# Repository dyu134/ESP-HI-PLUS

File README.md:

# ESP-HI-PLUS

An **AI-enabled voice assistant with on-screen interaction**, built around the **ESP32-S3-WROOM-1**. The board integrates a microphone, speaker amplifier, IMU, 2" IPS LCD, MicroSD card slot, and USB-C with on-board Li-ion battery charging, and exposes **two 5-pin magnetic pogo-pin connectors** for attaching various sub-modules. Designed for handheld and wearable applications that combine on-device conversational AI, audio capture/playback, display feedback, and motion sensing.

## Features

### Core Compute

- **ESP32-S3-WROOM-1** (U2) — 32-bit dual-core LX7 MCU with Wi-Fi 4, BLE 5 (LE), and a rich peripheral set including I2S, I2C, SPI, and USB.

### Sensors

- **LSM6DSV16X** 6-axis IMU (U8) — 3-axis accelerometer + 3-axis gyroscope with I3C/I2C/SPI interface for motion tracking.
- **ICS-43434 I2S Microphone** (MK1) — digital MEMS microphone over I2S for audio capture.

### Audio Output

- **MAX98357A** Class-D I2S amplifier (U7) — drives an external speaker (LS1) with no required MCLK.
- **PicoBlade speaker connector** (LS1) for an off-board speaker.

### Power

- **USB-C input** (J1) with **USBLC6-2P6** ESD protection (D1/D7/D8).
- **TP4065** linear Li-ion/Li-Po charger (U5) — single-cell charging from USB.
- **TLV75733PDBV** 3.3 V LDO (U3) — system rail for the MCU and logic.
- **MAX40200AUK** ideal-diode OR-ing (U1, U6) — seamless USB / battery switching with low dropout.
- **PicoBlade battery connector** (BT1) for a single-cell Li-ion / Li-Po pack.
- **PMEG4010CEJ** Schottky diode (D5) and **MF-MSMF200** PTC fuse (F1) for input/battery protection.
- **SMF6.8CA** TVS diode (D6) for transient suppression.

### User Interface

- **[2" LCD header](https://www.waveshare.com/2inch-LCD-Module.htm)** (J2) — 2" IPS LCD display.
- **MicroSD Card Slot** (J5) — for local storage of audio, logs, or assets.
- **Two SKRPACE010 tactile pushbuttons** (SW1, SW2).
- **JS102011SAQN SPDT slide switch** (SW3).
- **WS2812B-2020** addressable RGB LED (D12), plus discrete status LEDs (D2 orange for battery charging, D4 red for USB power).
- **Two PR5L4015-5P-C-F magnetic pogo-pin connectors** (J3, J4) — 5-pin 2.54 mm headers that mate with **magnetic pogo-pin sub-modules** for snap-on expansion.

### Mounting

- Four M2 slim mounting holes (H1–H4).

## Sub-Module Identification

The ESP-HI-PLUS uses a two-stage detection system (analog ID resistor + I²C EEPROM metadata) to identify and configure attached sub-modules.

Detailed technical specifications for the identification protocol, class table, and EEPROM metadata can be found in the [Sub-modules directory](./Sub-modules/README.md).

## Available Sub-modules

- **[Desktop](./Sub-modules/Desktop/README.md)** — A desktop alarm clock and environment monitor featuring temperature, humidity, and presence sensing.

See the [Sub-modules directory](./Sub-modules/README.md) for technical specifications and the full list of supported classes.

## Repository Layout

```text
.
├── ESP-HI-PLUS.kicad_pro       # KiCad project file
├── ESP-HI-PLUS.kicad_sch       # Schematic
├── ESP-HI-PLUS.kicad_pcb       # PCB layout
├── Sub-modules/                # Snap-on expansion boards
│   └── Desktop/                # Desktop alarm clock / environment monitor
├── fp-lib-table                # Footprint library table
├── sym-lib-table               # Symbol library table
├── fabrication-toolkit-options.json
├── ESP-HI-PLUS Symbols/        # Project-local schematic symbols
├── ESP-HI-PLUS Footprints/     # Project-local footprint libraries (*.pretty)
├── ESP-HI-PLUS 3D Models/      # STEP models used by the 3D viewer
├── production/                 # Manufacturing outputs
    ├── bom.csv                 # Bill of materials
    ├── designators.csv         # Reference designators
    ├── positions.csv           # Pick-and-place positions
    ├── netlist.ipc             # IPC-D-356 netlist
    └── ESP-HI-PLUS_v1.17.zip   # Production archive (latest)
```

## Bill of Materials (summary)

| Refs        | Description                                                                                  |
|-------------|----------------------------------------------------------------------------------------------|
| U2          | ESP32-S3-WROOM-1 module                                                                      |
| U3          | TLV75733PDBV — 3.3 V LDO                                                                     |
| U5          | TP4065 — Li-ion charger                                                                      |
| MK1         | ICS-43434 I2S microphone                                                                     |
| U7          | MAX98357A — I2S Class-D amplifier                                                            |
| U8          | LSM6DSV16X — 6-axis IMU                                                                      |
| U1, U6      | MAX40200AUK — ideal diode                                                                    |
| D1/D7/D8    | USBLC6-2P6 — USB ESD TVS array                                                               |
| D12         | WS2812B-2020 — addressable RGB LED                                                           |
| J1          | USB-C receptacle                                                                             |
| J2          | [2" IPS LCD connector](https://www.waveshare.com/2inch-LCD-Module.htm)                       |
| J3, J4      | Two 5-pin magnetic pogo-pin connectors (PR5L4015-5P-C-F) for sub-modules                     |
| J5          | MicroSD Card Slot (Hirose DM3AT)                                                             |
| SW1, SW2    | SKRPACE010 tactile pushbuttons                                                               |
| SW3         | JS102011SAQN SPDT slide switch                                                               |
| R28, R29    | 47 kΩ sub-module **AUX1/ID0** detection resistors (0402) — divider used for ADC class lookup |

See `production/bom.csv` for the full BOM with footprints and quantities.

## Getting Started

1. Open `ESP-HI-PLUS.kicad_pro` in KiCad 8 or later.
2. Review the schematic (`ESP-HI-PLUS.kicad_sch`) and PCB (`ESP-HI-PLUS.kicad_pcb`).
3. Re-generate fabrication outputs as needed (Gerbers, drill files, pick-and-place).
4. Flash the ESP32-S3 via the USB-C port using ESP-IDF or Arduino.

## Manufacturing Outputs

The `production/` folder contains ready-to-use outputs for the latest **v1.17** revision:

- **`bom.csv`** — bill of materials for sourcing.
- **`positions.csv`** — pick-and-place rotation/coordinates for SMT assembly.
- **`netlist.ipc`** — IPC-D-356 test netlist.
- **`ESP-HI-PLUS_v1.17.zip`** — full fabrication archive (Gerbers + drill included).

## License

License not specified. Add a `LICENSE` file if you intend to distribute this design.

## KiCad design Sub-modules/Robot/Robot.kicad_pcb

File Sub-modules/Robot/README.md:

# Robot Sub-module

The **Robot** sub-module is a high-performance actuator and sensing expansion board for the **ESP-HI-PLUS**, designed to transform the device into a mobile or interactive robotic platform. Powered by an RP2040 MCU, it handles real-time motor control, battery management, and inertial sensing.

*(Space for 3D Model Image)*

## Features

### Core Compute

- **RP2040** (U3) — Dual-core ARM Cortex-M0+ microcontroller for real-time servo PWM generation and sensor processing.
- **16 Mbit Flash** (U?) — Storage for RP2040 firmware.

### Actuation & Sensing

- **Servo Support** (M1–M4) — High-current outputs for up to 4 high-torque servo motors (e.g., MG996R).
- **LSM6DSV16X** (U8) — 6-axis IMU with embedded sensor fusion and Machine Learning Core for orientation and motion detection.
- **INA3221** (U11) — Triple-channel current and voltage monitor for real-time tracking of servo and system power consumption.

### Power Management

- **TLV75733PDBV** (U4) — 3.3V Low-Dropout (LDO) regulator providing stable power to the MCU and peripherals.
- **MAX17049** (U5) — 2-cell Li-ion battery fuel gauge with ModelGauge m5 algorithm for accurate state-of-charge reporting.
- **MAX40200AUK** (U2) — Ultra-low voltage drop ideal diode for efficient power path management.
- **UBEC Input** — Support for external 5V UBEC to power high-current servos from the battery.
- **XT60 Connector** (J4) — High-current battery interface (typically 2S Li-ion).

### User Interface & IO

- **SK9822-EC20** (D6) — Addressable RGB LED for status or mood lighting.
- **SKRPACE010** (SW3, SW?) — Tactile switches for reset, boot mode, or user interaction.

### Identification & Metadata

The Robot module follows the standard [ESP-HI-PLUS identification protocol](../README.md).

- **R_ID (953 kΩ)** — Identifies the module as **Class 1 (Actuator — Servo)**.
- **AT24CS02** (U10) — 2 Kbit I²C EEPROM carrying module metadata and serial number.

#### EEPROM Metadata

| Offset | Size | Field | Value (Hex) | Value (Decoded) | Description |
| :------: | :----: | :------ | :-----------: | :---------------- | :------------ |
| 0x00 | 4 | Magic Number | 45 53 50 4D | "ESPM" | ASCII sanity check |
| 0x04 | 1 | Class ID | 0x01 | 1 | Actuator - Servo |
| 0x05 | 1 | Module ID | 0x03 | 3 | Robot v1 |
| 0x06 | 1 | HW Revision | 0x01 | 1 | First PCB revision |
| 0x07 | 2 | FW Revision | 0x0100 | 1.0 | Major.Minor |
| 0x09 | 1 | Protocol Revision | 0x01 | 1 | Communication protocol v1 |
| 0x0A | 1 | Power Requirement | 0x00 | Self-powered | Powered by 2S battery |
| 0x0B | 2 | Max Current (mA) | 0x07D0 | 2000 mA | Maximum draw (little-endian) |
| 0x0D | 2 | Min Voltage (mV) | 0x1770 | 6000 mV | Minimum supply voltage (2S) |
| 0x0F | 2 | Boot Delay (ms) | 0x0064 | 100 ms | Power-on delay (little-endian) |
| 0x11 | 4 | Capability Bitmask | 0x00000014 | — | Bits 2, 4 enabled (Async, E-Stop) |
| 0x15 | 16 | Module Name | 52 6F 62 6F... | "Robot" | ASCII, null-terminated |
| 0x25 | 16 | Serial Number | 52 42 2D 30... | "RB-001-XXXX" | ASCII, null-terminated |
| 0x35 | 198 | User Data | — | — | Available for custom data |
| 0xFB | 4 | CRC32 | 0xXXXXXXXX | — | CRC32 of bytes 0x00–0xFA |

#### Capability Bitmask (Proposed)

**Value:** `0x00000014`

| Bit | Value | Capability | Status |
| :---: | :---: | :--- | :--- |
| 0 | 0x01 | Needs Calibration | ❌ Disabled |
| 1 | 0x02 | Requires ACK | ❌ Disabled |
| 2 | 0x04 | Async Data | ✅ Enabled |
| 3 | 0x08 | Supports Sleep | ❌ Disabled |
| 4 | 0x10 | Has Emergency Stop | ✅ Enabled |
| 5 | 0x20 | Supports OTA | ❌ Disabled |
| 6 | 0x40 | Has Battery Backup | ❌ Disabled |
| 7 | 0x80 | Requires Bootloader Mode | ❌ Disabled |

## Integration

The Robot module uses an RP2040 to handle low-level PWM and sensor data. It communicates with the ESP-HI-PLUS main board via UART and I²C.

### Pinouts (Magnetic Pogo Connectors)

#### J2 (MAG1)

| Pin | Name   | Description                                           |
| --- | ------ | ----------------------------------------------------- |
| 1   | VMAIN  | 2-way power bus shared with main module               |
| 2   | GND    | Ground                                                |
| 3   | UART RX| Data from main module                                 |
| 4   | UART TX| Data to main module                                   |
| 5   | EN     | Main module control to enable/disable submodule power |

#### J3 (MAG2)

| Pin | Name     | Description                                     |
| --- | -------- | ----------------------------------------------- |
| 1   | I2C SDA  | For reading module ID metadata EEPROM           |
| 2   | I2C SCL  | For reading module ID metadata EEPROM           |
| 3   | AUX1/ID0 | Hardware class identifier resistor              |
| 4   | AUX2     | Auxiliary data pin                              |
| 5   | AUX3     | Auxiliary data pin                              |

## Repository Layout

```text
.
├── Robot.kicad_pro           # KiCad project file
├── Robot.kicad_sch           # Schematic
├── Robot.kicad_pcb           # PCB layout
├── Robot Symbols/            # Project-local schematic symbols
└── README.md                 # This file
```

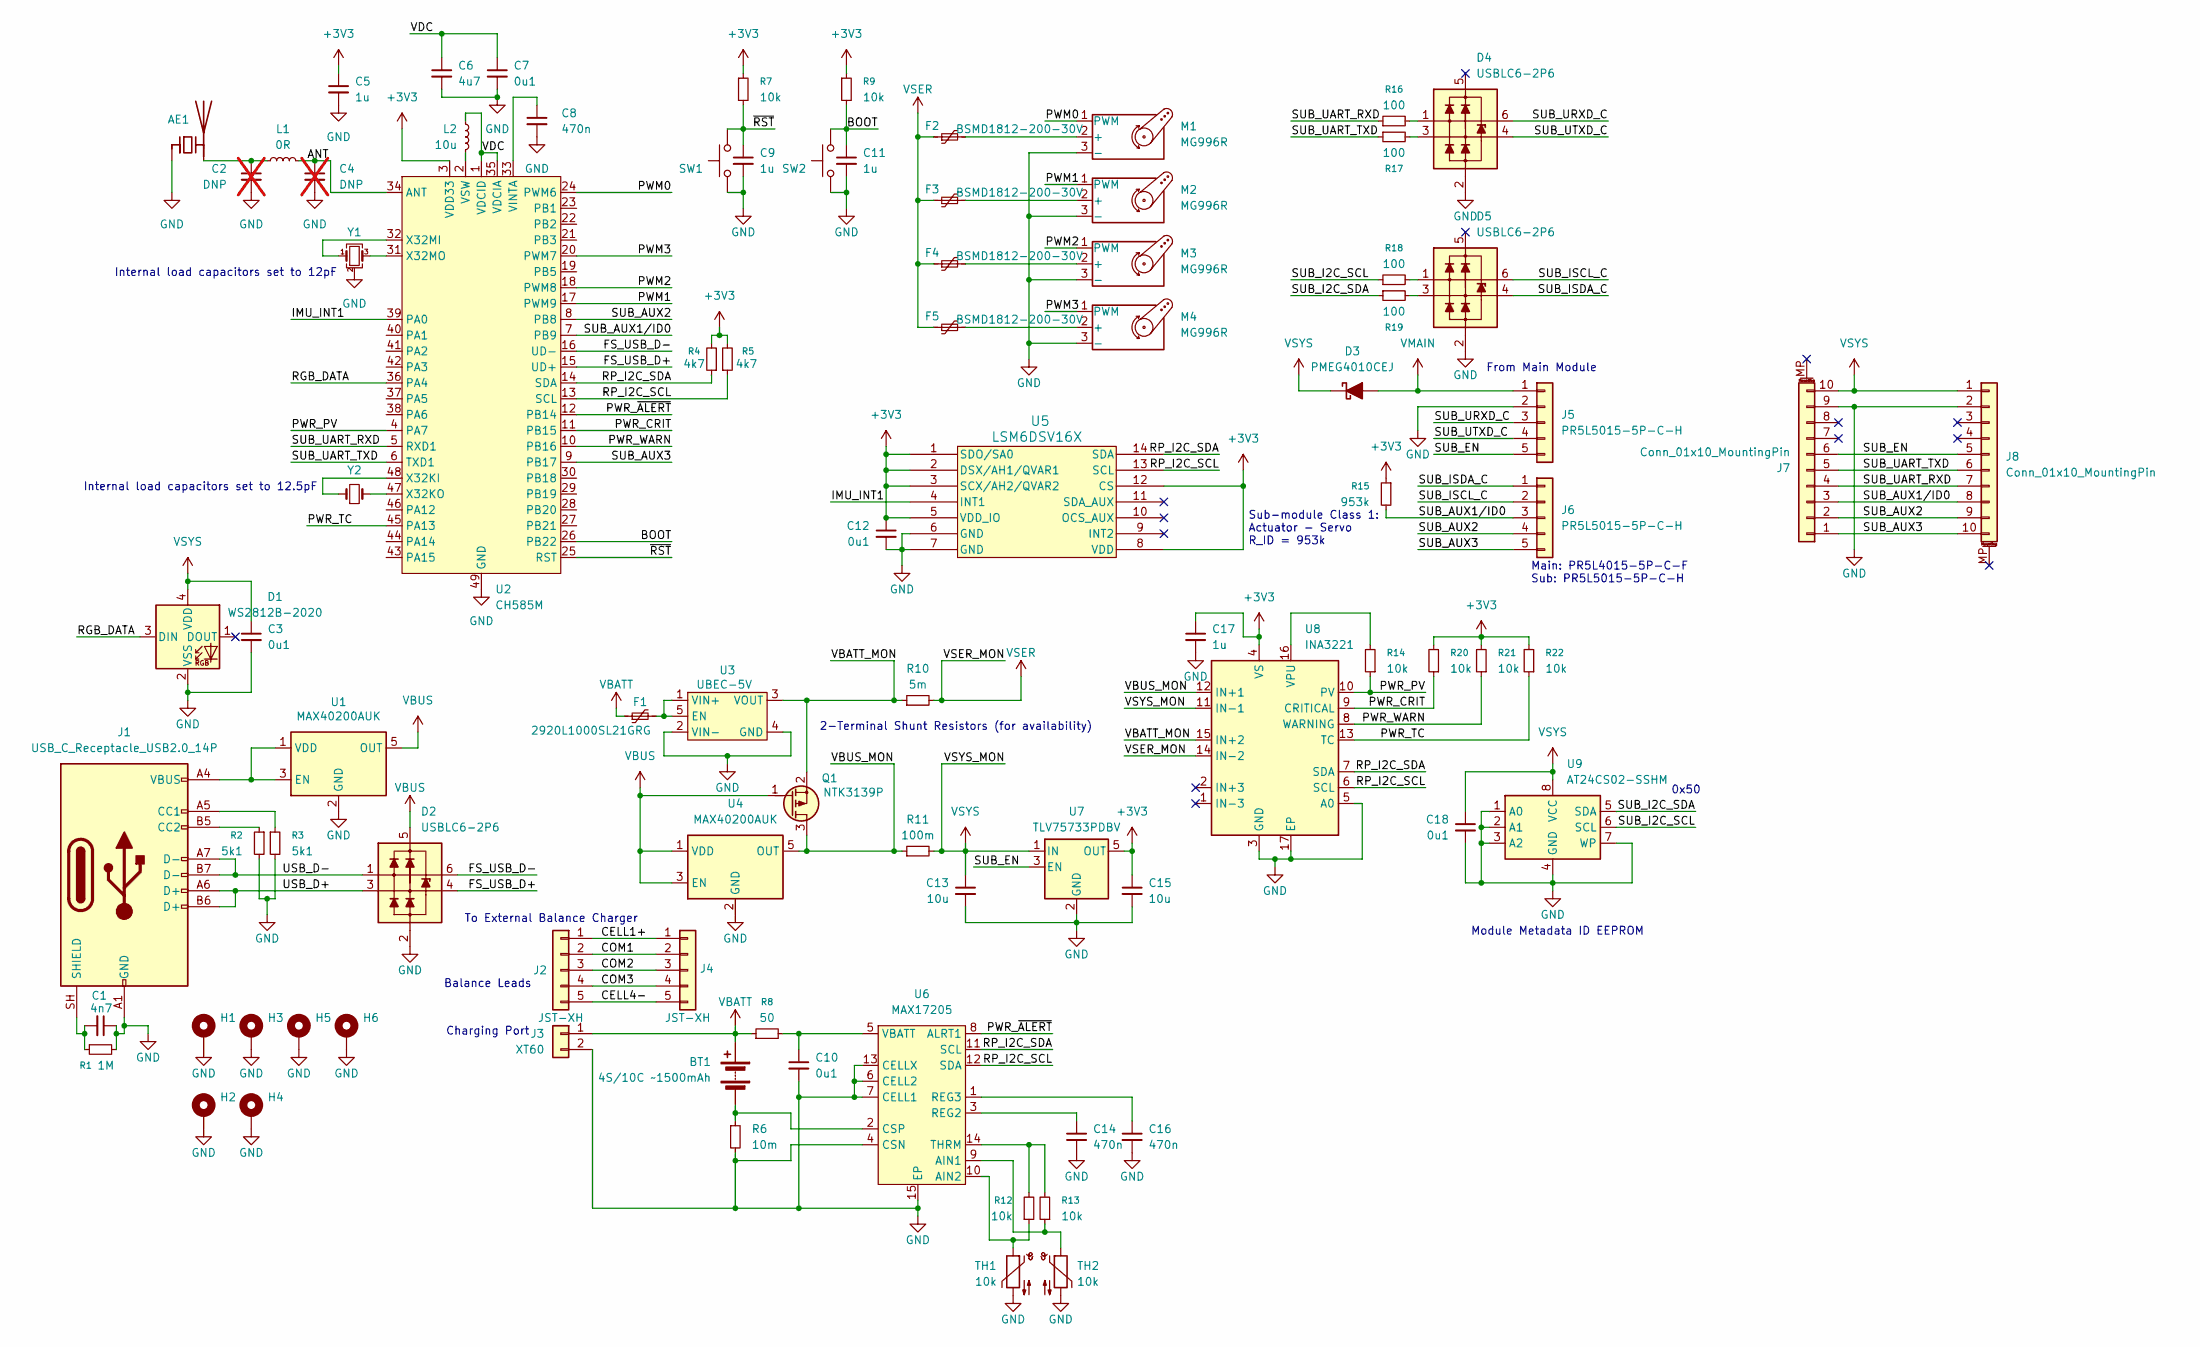
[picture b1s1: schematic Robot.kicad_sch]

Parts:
AE1: Antenna_Chip; Johanson_2450AT18x100
BT1: 4S/10C ~1500mAh; AMASS_XT60-F_1x02_P7.20mm_Vertical
C1: 4n7; C_0402_1005Metric
C2, C4: DNP; C_0402_1005Metric; not fitted
C3, C7, C10, C12, C18: 0u1; C_0402_1005Metric
C5, C9, C11, C17: 1u; C_0402_1005Metric
C6: 4u7; C_0402_1005Metric
C8, C14, C16: 470n; C_0402_1005Metric
C13, C15: 10u; C_0402_1005Metric
D1: WS2812B-2020; LED_WS2812B-2020_PLCC4_2.0x2.0mm
D2, D4, D5: USBLC6-2P6; SOT-666
D3: PMEG4010CEJ; D_SOD-323F
F1: 2920L1000SL21GRG; Fuse_2920_7451Metric
F2, F3, F4, F5: BSMD1812-200-30V; Fuse_1812_4532Metric
H1, H2, H3, H4, H5, H6: MountingHole_Pad_MP; MountingHole_M3_Slim
J1: USB_C_Receptacle_USB2.0_14P; USB_C_Receptacle_HCTL_HC-TYPE-C-16P-01A
J2: JST-XH; JST_XH_S5B-XH-A_1x05_P2.50mm_Horizontal
J3: XT60; AMASS_XT60PW-M_1x02_P7.20mm_Horizontal
J4: JST-XH; JST_XH_B5B-XH-A_1x05_P2.50mm_Vertical
J5, J6: PR5L5015-5P-C-H; PinHeader_1x05_P2.54mm_Vertical
J7, J8: Conn_01x10_MountingPin; Hirose_FH12-10S-0.5SH_1x10-1MP_P0.50mm_Horizontal
L1: 0R; R_0402_1005Metric
L2: 10u; L_0805_2012Metric
M1, M2, M3, M4: MG996R; PinHeader_1x03_P2.54mm_Vertical
Q1: NTK3139P; SOT-723
R1: 1M; R_0402_1005Metric
R2, R3: 5k1; R_0402_1005Metric
R4, R5: 4k7; R_0402_1005Metric
R6: 10m; R_1206_3216Metric
R7, R9, R12, R13, R14, R20, R21, R22: 10k; R_0402_1005Metric
R8: 50; R_0402_1005Metric
R10: 5m; R_1206_3216Metric
R11: 100m; R_1206_3216Metric
R15: 953k; R_0402_1005Metric
R16, R17, R18, R19: 100; R_0402_1005Metric
SW1, SW2: SKRPACE010; SW_Push_1P1T_NO_Vertical_Wuerth_434133025816
TH1, TH2: 10k; R_0603_1608Metric
U1, U4: MAX40200AUK; SOT-23-5
U2: CH585M; QFN-48_EP_5x5_Pitch0.35mm
U3: UBEC-5V
U5: LSM6DSV16X; LGA14_LSM6_STM
U6: MAX17205; TDFN-14-1EP_3x3mm_P0.4mm_EP1.78x2.35mm
U7: TLV75733PDBV; SOT-23-5
U8: INA3221; Texas_RGV0016A_VQFN-16-1EP_4x4mm_P0.65mm_EP2.1x2.1mm
U9: AT24CS02-SSHM; SOIC-8_3.9x4.9mm_P1.27mm
Y1: XL7EL89COI-111YLC-32M; Crystal_SMD_2016-4Pin_2.0x1.6mm
Y2: Q13FC13500004; Crystal_SMD_3215-2Pin_3.2x1.5mm

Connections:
+3V3: C5.1, C12.1, C15.1, C17.1, R4.2, R5.2, R7.1, R9.1, R15.1, R20.2, R21.2, R22.2, U2.3 (VDD33), U5.1 (SDO/SA0), U5.2 (DSX/AH1/QVAR1), U5.3 (SCX/AH2/QVAR2), U5.5 (VDD_IO), U5.8 (VDD), U5.12 (CS), U7.5 (OUT), U8.4 (VS)
/ANT: C4.1, L1.2, U2.34 (ANT)
/BOOT: C11.1, R9.2, SW2.2, U2.26 (PB22)
/CELL1+: J2.1, J4.1
/CELL4-: J2.5, J4.5
/COM1: J2.2, J4.2
/COM2: J2.3, J4.3
/COM3: J2.4, J4.4
/FS_USB_D+: D2.4 (L2), U2.15 (UD+)
/FS_USB_D-: D2.6 (L1), U2.16 (UD-)
/IMU_INT1: U2.39 (PA0), U5.4 (INT1)
/PWM0: M1.1 (PWM), U2.24 (PWM6)
/PWM1: M2.1 (PWM), U2.17 (PWM9)
/PWM2: M3.1 (PWM), U2.18 (PWM8)
/PWM3: M4.1 (PWM), U2.20 (PWM7)
/PWR_CRIT: R20.1, U2.11 (PB15), U8.9 (CRITICAL)
/PWR_PV: R14.1, U2.4 (PA7), U8.10 (PV)
/PWR_TC: R22.1, U2.45 (PA13), U8.13 (TC)
/PWR_WARN: R21.1, U2.10 (PB16), U8.8 (WARNING)
/PWR_~ALERT: U2.12 (PB14), U6.8 (ALRT1)
/RGB_DATA: D1.3 (DIN), U2.36 (PA4)
/RP_I2C_SCL: R5.1, U2.13 (SCL), U5.13 (SCL), U6.12 (SDA), U8.6 (SCL)
/RP_I2C_SDA: R4.1, U2.14 (SDA), U5.14 (SDA), U6.11 (SCL), U8.7 (SDA)
/SUB_AUX1/ID0: J6.3, J7.3, J8.8, R15.2, U2.7 (PB9)
/SUB_AUX2: J6.4, J7.2, J8.9, U2.8 (PB8)
/SUB_AUX3: J6.5, J7.1, J8.10, U2.9 (PB17)
/SUB_EN: J5.5, J7.6, J8.5, U7.3 (EN)
/SUB_I2C_SCL: R18.1, U9.6 (SCL)
/SUB_I2C_SDA: R19.1, U9.5 (SDA)
/SUB_ISCL_C: D5.6 (L1), J6.2
/SUB_ISDA_C: D5.4 (L2), J6.1
/SUB_UART_RXD: J7.4, J8.7, R16.1, U2.5 (RXD1)
/SUB_UART_TXD: J7.5, J8.6, R17.1, U2.6 (TXD1)
/SUB_URXD_C: D4.6 (L1), J5.3
/SUB_UTXD_C: D4.4 (L2), J5.4
/USB_D+: D2.3 (L2), J1.A6 (D+), J1.B6 (D+)
/USB_D-: D2.1 (L1), J1.A7 (D-), J1.B7 (D-)
/VBATT_MON: Q1.2 (S), R10.1, U3.3 (VOUT), U8.15 (IN+2)
/VBUS_MON: Q1.3 (D), R11.1, U4.5 (OUT), U8.12 (IN+1)
/VDC: C6.1, C7.1, L2.2, U2.1 (VDCID), U2.35 (VDCIA)
/~RST: C9.1, R7.2, SW1.2, U2.25 (RST)
GND: AE1.1 (FEED), C1.1, C2.2, C3.2, C4.2, C5.2, C6.2, C7.2, C8.2, C9.2, C10.2, C11.2, C12.2, C13.2, C14.2, C15.2, C16.2, C17.2, C18.2, D1.2 (VSS), D2.2 (VN), D4.2 (VN), D5.2 (VN), H1.MP (MP_MP), H2.MP (MP_MP), H3.MP (MP_MP), H4.MP (MP_MP), H5.MP (MP_MP), H6.MP (MP_MP), J1.A1 (GND), J1.A12 (GND), J1.B1 (GND), J1.B12 (GND), J3.2, J5.2, J7.9, J8.2, M1.3 (-), M2.3 (-), M3.3 (-), M4.3 (-), R1.2, R2.2, R3.2, R6.2, SW1.1, SW2.1, TH1.2, TH2.2, U1.2 (GND), U2.49 (GND), U3.2 (VIN-), U3.4 (GND), U4.2 (GND), U5.6 (GND), U5.7 (GND), U6.4 (CSN), U6.6 (CELL2), U6.7 (CELL1), U6.13 (CELLX), U6.15 (EP), U7.2 (GND), U8.3 (GND), U8.5 (A0), U8.17 (EP), U9.1 (A0), U9.2 (A1), U9.3 (A2), U9.4 (GND), U9.7 (WP), Y1.2 (G), Y1.4 (G)
unnamed: AE1.2 (PCB_Trace), C2.1, L1.1
unnamed: BT1.2 (-), R6.1, U6.2 (CSP)
unnamed: D4.1 (L1), R16.2
unnamed: D4.3 (L2), R17.2
unnamed: D5.1 (L1), R18.2
unnamed: D5.3 (L2), R19.2
unnamed: J1.A5 (CC1), R3.1
unnamed: J1.B5 (CC2), R2.1
unnamed: C1.2, J1.SH (SHIELD), R1.1
unnamed: F2.2, M1.2 (+)
unnamed: F3.2, M2.2 (+)
unnamed: F4.2, M3.2 (+)
unnamed: F5.2, M4.2 (+)
unnamed: J1.A4 (VBUS), J1.A9 (VBUS), J1.B4 (VBUS), J1.B9 (VBUS), U1.1 (VDD), U1.3 (EN)
unnamed: U2.48 (X32KI), Y2.1
unnamed: U2.47 (X32KO), Y2.2
unnamed: C8.1, U2.33 (VINTA)
unnamed: L2.1, U2.2 (VSW)
unnamed: U2.32 (X32MI), Y1.1
unnamed: U2.31 (X32MO), Y1.3
unnamed: F1.2, U3.1 (VIN+), U3.5 (EN)
unnamed: R13.1, TH2.1, U6.9 (AIN1)
unnamed: R12.1, TH1.1, U6.10 (AIN2)
unnamed: C14.1, U6.3 (REG2)
unnamed: C16.1, U6.1 (REG3)
unnamed: R12.2, R13.2, U6.14 (THRM)
unnamed: C10.1, R8.2, U6.5 (VBATT)
unnamed: R14.2, U8.16 (VPU)
VBATT: BT1.1 (+), F1.1, J3.1, R8.1
VBUS: D2.5 (VP), Q1.1 (G), U1.5 (OUT), U4.1 (VDD), U4.3 (EN)
VMAIN: D3.2 (A), J5.1
VSER: F2.1, F3.1, F4.1, F5.1, R10.2, U8.14 (IN-2)
VSYS: C3.1, C13.1, C18.1, D1.4 (VDD), D3.1 (K), J7.10, J8.1, R11.2, U7.1 (IN), U8.11 (IN-1), U9.8 (VCC)

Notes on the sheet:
From Main Module
2-Terminal Shunt Resistors (for availability)
Internal load capacitors set to 12pF
Sub-module Class 1: Actuator - Servo R_ID = 953k
Charging Port
To External Balance Charger
Internal load capacitors set to 12.5pF
Module Metadata ID EEPROM
0x50
Main: PR5L4015-5P-C-F Sub: PR5L5015-5P-C-H
Balance Leads

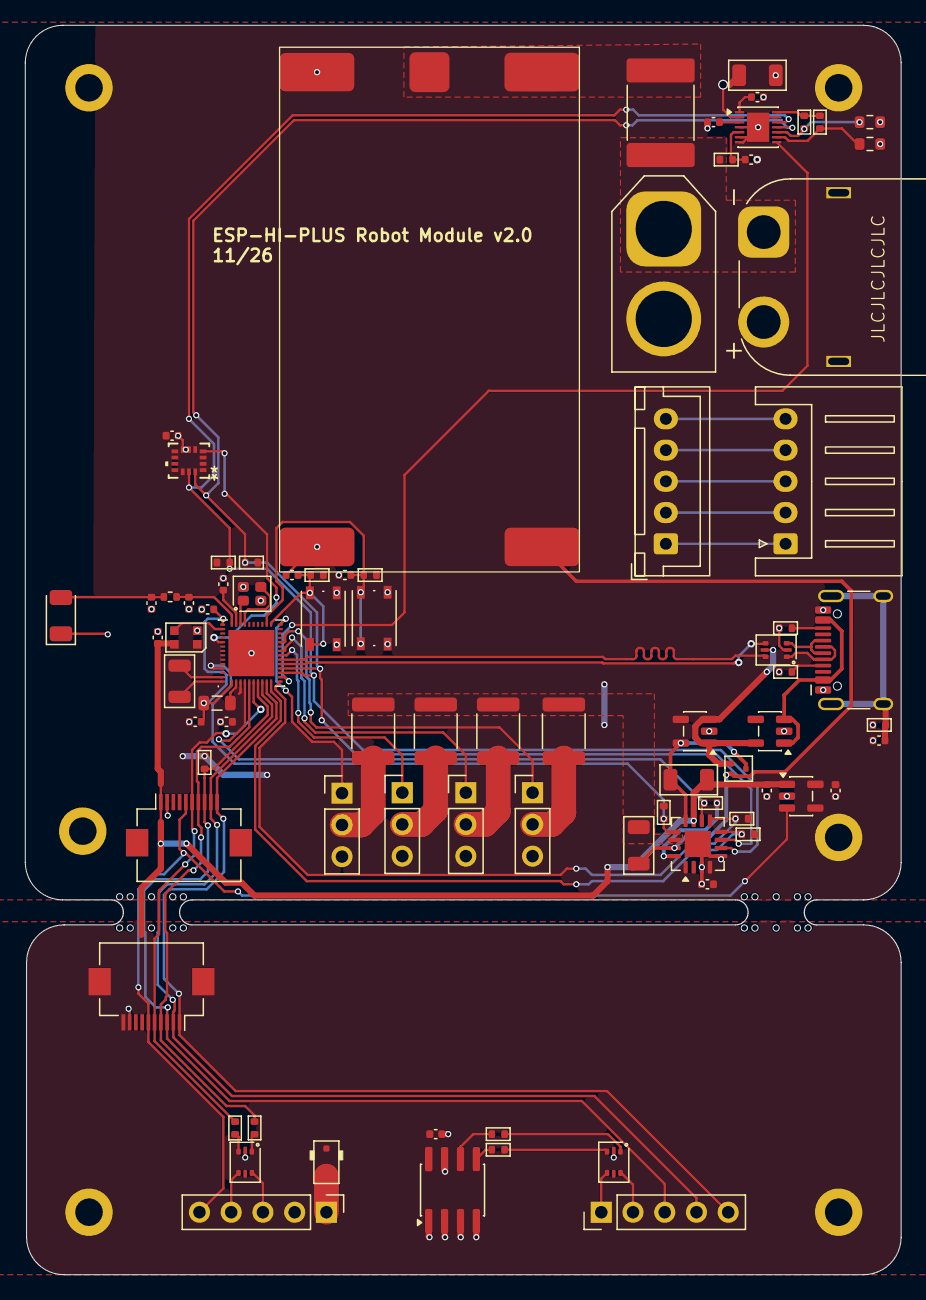
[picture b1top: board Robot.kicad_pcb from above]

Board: 2 copper layers, 70.1 x 100.0 mm, 88 parts (0 on the bottom side), 75 nets.

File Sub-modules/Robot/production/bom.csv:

Designator,Footprint,Quantity,Value,LCSC Part #
AE1,Johanson_2450AT18x100,1,Antenna_Chip,
BT1,AMASS_XT60-F_1x02_P7.20mm_Vertical,1,4S/10C ~1500mAh,
C1,0402,1,4n7,
"C10, C12, C18, C3, C7",0402,5,0u1,
"C11, C17, C5, C9",0402,4,1u,
"C13, C15",0402,2,10u,
"C14, C16, C8",0402,3,470n,
C6,0402,1,4u7,
D1,LED_WS2812B-2020_PLCC4_2.0x2.0mm,1,WS2812B-2020,
"D2, D4, D5",SOT-666,3,USBLC6-2P6,
D3,D_SOD-323F,1,PMEG4010CEJ,
F1,2920,1,2920L1000SL21GRG,
"F2, F3, F4, F5",1812,4,BSMD1812-200-30V,
J1,USB_C_Receptacle_HCTL_HC-TYPE-C-16P-01A,1,USB_C_Receptacle_USB2.0_14P,
J2,JST_XH_S5B-XH-A_1x05_P2.50mm_Horizontal,1,JST-XH,
J3,AMASS_XT60PW-M_1x02_P7.20mm_Horizontal,1,XT60,
J4,JST_XH_B5B-XH-A_1x05_P2.50mm_Vertical,1,JST-XH,
"J5, J6",PinHeader_1x05_P2.54mm_Vertical,2,PR5L5015-5P-C-H,
"J7, J8",Hirose_FH12-10S-0.5SH_1x10-1MP_P0.50mm_Horizontal,2,Conn_01x10_MountingPin,
L1,0402,1,0R,
L2,0805,1,10u,
"M1, M2, M3, M4",PinHeader_1x03_P2.54mm_Vertical,4,MG996R,
Q1,SOT-723,1,NTK3139P,
R1,0402,1,1M,
R10,1206,1,5m,
R11,1206,1,100m,
"R12, R13, R14, R20, R21, R22, R7, R9",0402,8,10k,
R15,0402,1,953k,
"R16, R17, R18, R19",0402,4,100,
"R2, R3",0402,2,5k1,
"R4, R5",0402,2,4k7,
R6,1206,1,10m,
R8,0402,1,50,
"SW1, SW2",SW_Push_1P1T_NO_Vertical_Wuerth_434133025816,2,SKRPACE010,
"TH1, TH2",0603,2,10k,
"U1, U4",SOT-23-5,2,MAX40200AUK,
U2,QFN-48_EP_5x5_Pitch0.35mm,1,CH585M,
U3,UBEC-5V,1,UBEC-5V,
U5,LGA14_LSM6_STM,1,LSM6DSV16X,
U6,TDFN-14-1EP_3x3mm_P0.4mm_EP1.78x2.35mm,1,MAX17205,
U7,SOT-23-5,1,TLV75733PDBV,
U8,Texas_RGV0016A_VQFN-16-1EP_4x4mm_P0.65mm_EP2.1x2.1mm,1,INA3221,
U9,SOIC-8_3.9x4.9mm_P1.27mm,1,AT24CS02-SSHM,
Y1,Crystal_SMD_2016-4Pin_2.0x1.6mm,1,XL7EL89COI-111YLC-32M,
Y2,Crystal_SMD_3215-2Pin_3.2x1.5mm,1,Q13FC13500004,

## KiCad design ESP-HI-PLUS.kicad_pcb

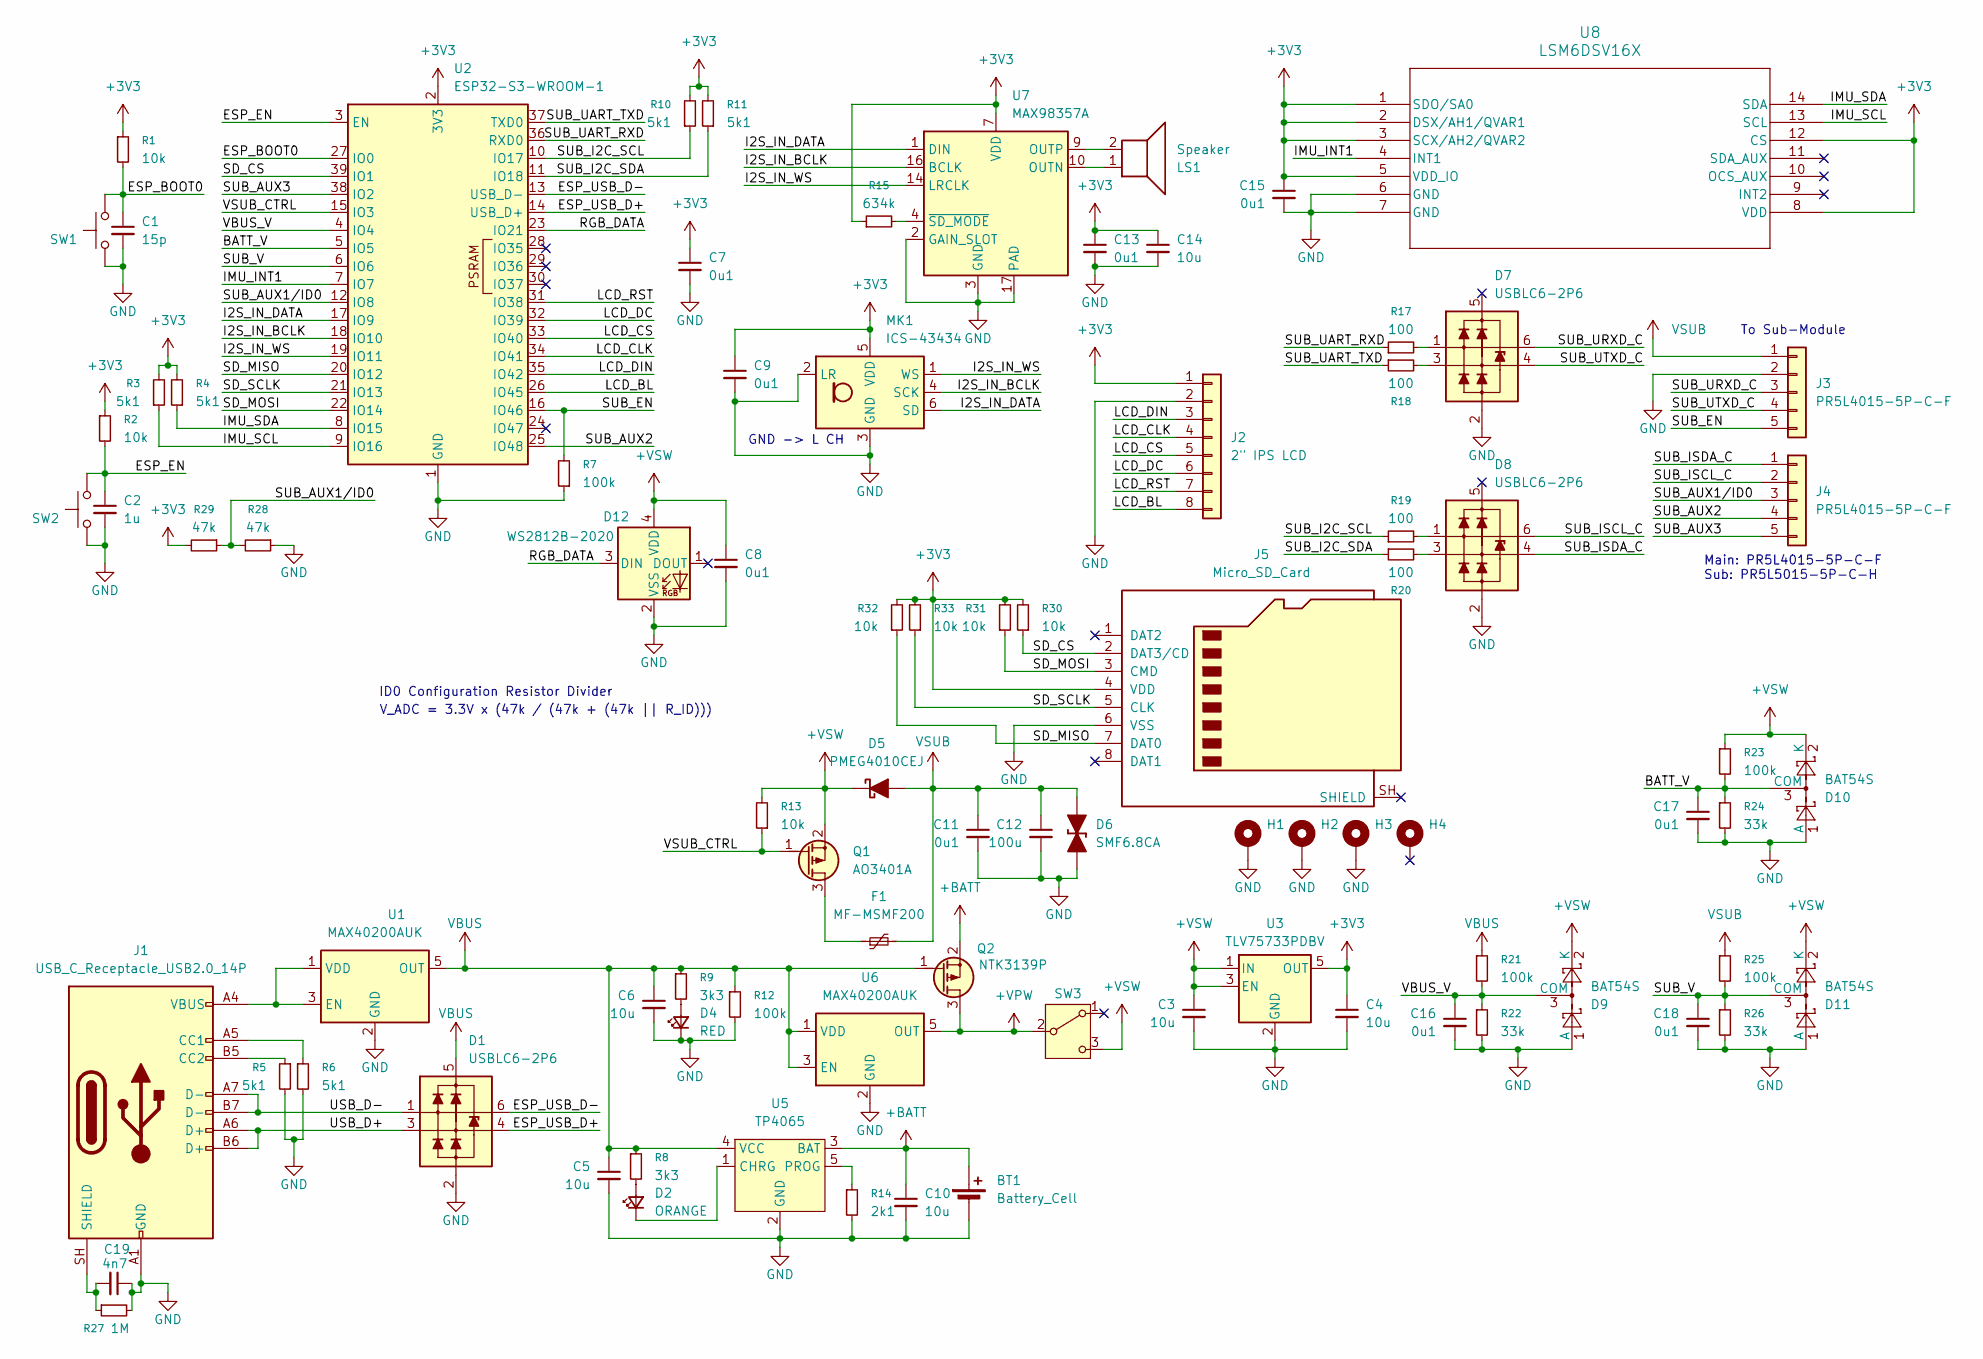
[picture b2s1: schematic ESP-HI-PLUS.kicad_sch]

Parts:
BT1: Battery_Cell; Molex_PicoBlade_53048-0210_1x02_P1.25mm_Horizontal
C1: 15p; C_0402_1005Metric
C2: 1u; C_0402_1005Metric
C3, C4, C5, C6, C10, C14: 10u; C_0402_1005Metric
C7, C8, C9, C11, C13, C15, C16, C17, C18: 0u1; C_0402_1005Metric
C12: 100u; C_0805_2012Metric
C19: 4n7; C_0402_1005Metric
D1, D7, D8: USBLC6-2P6; SOT-666
D2: ORANGE; LED_0603_1608Metric
D4: RED; LED_0603_1608Metric
D5: PMEG4010CEJ; D_SOD-323F
D6: SMF6.8CA; D_SOD-123F
D9, D10, D11: BAT54S; SOT-23
D12: WS2812B-2020; LED_WS2812B-2020_PLCC4_2.0x2.0mm
F1: MF-MSMF200; Fuse_1812_4532Metric
H1, H2, H3, H4: MountingHole_Pad_MP; MountingHole_M3_Slim
J1: USB_C_Receptacle_USB2.0_14P; USB_C_Receptacle_HCTL_HC-TYPE-C-16P-01A
J2: 2" IPS LCD; PinSocket_1x08_P2.54mm_Vertical
J3, J4: PR5L4015-5P-C-F; PinHeader_1x05_P2.54mm_Vertical
J5: Micro_SD_Card; microSD_HC_Hirose_DM3AT-SF-PEJM5
LS1: Speaker; Molex_PicoBlade_53048-0210_1x02_P1.25mm_Horizontal
MK1: ICS-43434; InvenSense_ICS-43434-6_3.5x2.65mm
Q1: AO3401A; SOT-23
Q2: NTK3139P; SOT-723
R1, R2, R13, R30, R31, R32, R33: 10k; R_0402_1005Metric
R3, R4, R5, R6, R10, R11: 5k1; R_0402_1005Metric
R7, R12, R21, R23, R25: 100k; R_0402_1005Metric
R8, R9: 3k3; R_0402_1005Metric
R14: 2k1; R_0402_1005Metric
R15: 634k; R_0402_1005Metric
R17, R18, R19, R20: 100; R_0402_1005Metric
R22, R24, R26: 33k; R_0402_1005Metric
R27: 1M; R_0402_1005Metric
R28, R29: 47k; R_0402_1005Metric
SW1, SW2: SKRPACE010; SW_Push_1P1T_NO_Vertical_Wuerth_434133025816
SW3: JS102011SAQN; SW_SPDT_CK_JS102011SAQN
U1, U6: MAX40200AUK; SOT-23-5
U2: ESP32-S3-WROOM-1
U3: TLV75733PDBV; SOT-23-5
U5: TP4065; SOT-23-5_HandSoldering
U7: MAX98357A; TQFN-16-1EP_3x3mm_P0.5mm_EP1.23x1.23mm
U8: LSM6DSV16X; LGA14_LSM6_STM

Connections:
+3V3: C4.1, C7.1, C9.1, C13.1, C14.1, C15.1, J2.1, J5.4 (VDD), MK1.5 (VDD), R1.1, R2.1, R3.2, R4.2, R10.2, R11.2, R15.1, R29.2, R30.2, R31.2, R32.2, R33.2, U2.2 (3V3), U3.5 (OUT), U7.7 (VDD), U7.8 (VDD), U8.1 (SDO/SA0), U8.2 (DSX/AH1/QVAR1), U8.3 (SCX/AH2/QVAR2), U8.5 (VDD_IO), U8.8 (VDD), U8.12 (CS)
+BATT: BT1.1 (+), C10.1, Q2.2 (S), U5.3 (BAT)
+VPW: Q2.3 (D), SW3.2 (B), U6.5 (OUT)
+VSW: C3.1, C8.1, D5.1 (K), D9.2 (K), D10.2 (K), D11.2 (K), D12.4 (VDD), Q1.2 (S), R13.2, R23.1, SW3.3 (C), U3.1 (IN), U3.3 (EN)
/BATT_V: C17.1, D10.3 (COM), R23.2, R24.1, U2.5 (IO5)
/ESP_BOOT0: C1.1, R1.2, SW1.2, U2.27 (IO0)
/ESP_EN: C2.1, R2.2, SW2.2, U2.3 (EN)
/ESP_USB_D+: D1.4 (L2), U2.14 (USB_D+)
/ESP_USB_D-: D1.6 (L1), U2.13 (USB_D-)
/I2S_IN_BCLK: MK1.4 (SCK), U2.18 (IO10), U7.16 (BCLK)
/I2S_IN_DATA: MK1.6 (SD), U2.17 (IO9), U7.1 (DIN)
/I2S_IN_WS: MK1.1 (WS), U2.19 (IO11), U7.14 (LRCLK)
/IMU_INT1: U2.7 (IO7), U8.4 (INT1)
/IMU_SCL: R3.1, U2.9 (IO16), U8.13 (SCL)
/IMU_SDA: R4.1, U2.8 (IO15), U8.14 (SDA)
/LCD_BL: J2.8, U2.26 (IO45)
/LCD_CLK: J2.4, U2.34 (IO41)
/LCD_CS: J2.5, U2.33 (IO40)
/LCD_DC: J2.6, U2.32 (IO39)
/LCD_DIN: J2.3, U2.35 (IO42)
/LCD_RST: J2.7, U2.31 (IO38)
/RGB_DATA: D12.3 (DIN), U2.23 (IO21)
/SD_CS: J5.2 (DAT3/CD), R30.1, U2.39 (IO1)
/SD_MISO: J5.7 (DAT0), R32.1, U2.20 (IO12)
/SD_MOSI: J5.3 (CMD), R31.1, U2.22 (IO14)
/SD_SCLK: J5.5 (CLK), R33.1, U2.21 (IO13)
/SUB_AUX1/ID0: J4.3, R28.2, R29.1, U2.12 (IO8)
/SUB_AUX2: J4.4, U2.25 (IO48)
/SUB_AUX3: J4.5, U2.38 (IO2)
/SUB_EN: J3.5, R7.2, U2.16 (IO46)
/SUB_I2C_SCL: R10.1, R19.1, U2.10 (IO17)
/SUB_I2C_SDA: R11.1, R20.1, U2.11 (IO18)
/SUB_ISCL_C: D8.6 (L1), J4.2
/SUB_ISDA_C: D8.4 (L2), J4.1
/SUB_UART_RXD: R17.1, U2.36 (RXD0)
/SUB_UART_TXD: R18.1, U2.37 (TXD0)
/SUB_URXD_C: D7.6 (L1), J3.3
/SUB_UTXD_C: D7.4 (L2), J3.4
/SUB_V: C18.1, D11.3 (COM), R25.2, R26.1, U2.6 (IO6)
/USB_D+: D1.3 (L2), J1.A6 (D+), J1.B6 (D+)
/USB_D-: D1.1 (L1), J1.A7 (D-), J1.B7 (D-)
/VBUS_V: C16.1, D9.3 (COM), R21.2, R22.1, U2.4 (IO4)
/VSUB_CTRL: Q1.1 (G), R13.1, U2.15 (IO3)
GND: BT1.2 (-), C1.2, C2.2, C3.2, C4.2, C5.2, C6.2, C7.2, C8.2, C9.2, C10.2, C11.2, C12.2, C13.2, C14.2, C15.2, C16.2, C17.2, C18.2, C19.1, D1.2 (VN), D4.1 (K), D6.1 (K), D7.2 (VN), D8.2 (VN), D9.1 (A), D10.1 (A), D11.1 (A), D12.2 (VSS), H1.MP (MP_MP), H2.MP (MP_MP), H3.MP (MP_MP), J1.A1 (GND), J1.A12 (GND), J1.B1 (GND), J1.B12 (GND), J2.2, J3.2, J5.6 (VSS), MK1.2 (LR), MK1.3 (GND), R5.2, R6.2, R7.1, R12.2, R14.2, R22.2, R24.2, R26.2, R27.2, R28.1, SW1.1, SW2.1, U1.2 (GND), U2.1 (GND), U2.40 (GND), U2.41 (GND), U3.2 (GND), U5.2 (GND), U6.2 (GND), U7.2 (GAIN_SLOT), U7.3 (GND), U7.11 (GND), U7.15 (GND), U7.17 (PAD), U8.6 (GND), U8.7 (GND)
unnamed: D2.2 (A), R8.2
unnamed: D2.1 (K), U5.1 (CHRG)
unnamed: D4.2 (A), R9.2
unnamed: D7.1 (L1), R17.2
unnamed: D7.3 (L2), R18.2
unnamed: D8.1 (L1), R19.2
unnamed: D8.3 (L2), R20.2
unnamed: J1.A5 (CC1), R6.1
unnamed: J1.B5 (CC2), R5.1
unnamed: C19.2, J1.SH (SHIELD), R27.1
unnamed: F1.1, Q1.3 (D)
unnamed: J1.A4 (VBUS), J1.A9 (VBUS), J1.B4 (VBUS), J1.B9 (VBUS), U1.1 (VDD), U1.3 (EN)
unnamed: R14.1, U5.5 (PROG)
unnamed: LS1.1, U7.10 (OUTN)
unnamed: LS1.2, U7.9 (OUTP)
unnamed: R15.2, U7.4 (~SD_MODE)
VBUS: C5.1, C6.1, D1.5 (VP), Q2.1 (G), R8.1, R9.1, R12.1, R21.1, U1.5 (OUT), U5.4 (VCC), U6.1 (VDD), U6.3 (EN)
VSUB: C11.1, C12.1, D5.2 (A), D6.2 (A), F1.2, J3.1, R25.1

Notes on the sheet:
V_ADC = 3.3V x (47k / (47k + (47k || R_ID)))
GND -> L CH
To Sub-Module
Main: PR5L4015-5P-C-F Sub: PR5L5015-5P-C-H
ID0 Configuration Resistor Divider

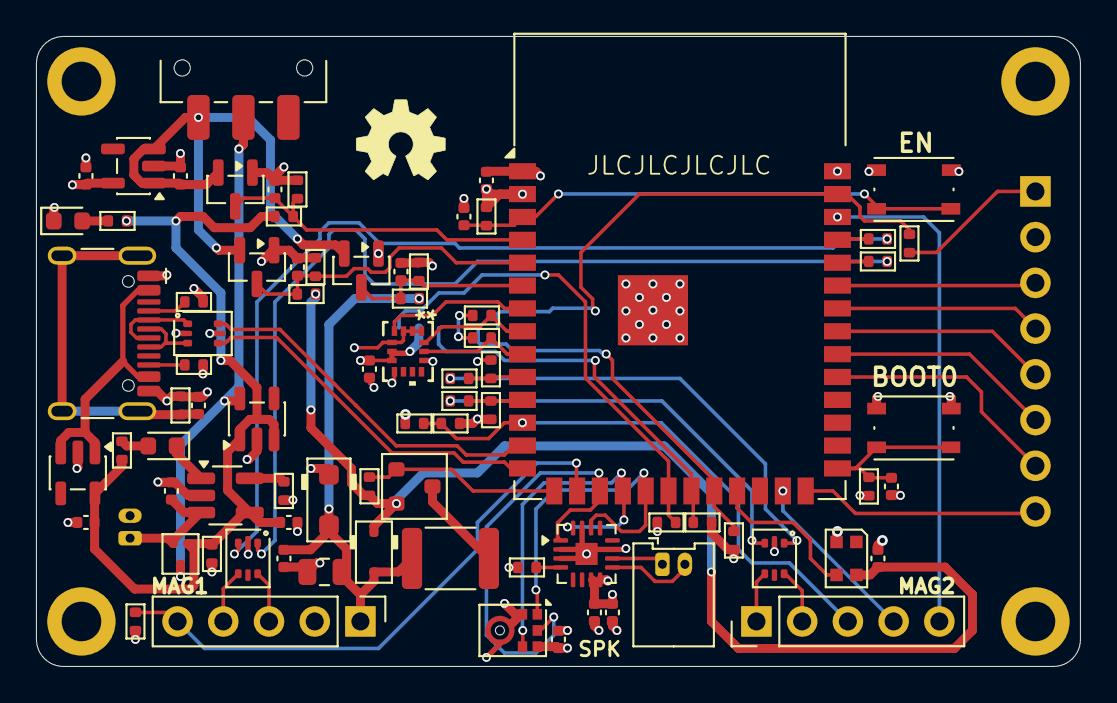
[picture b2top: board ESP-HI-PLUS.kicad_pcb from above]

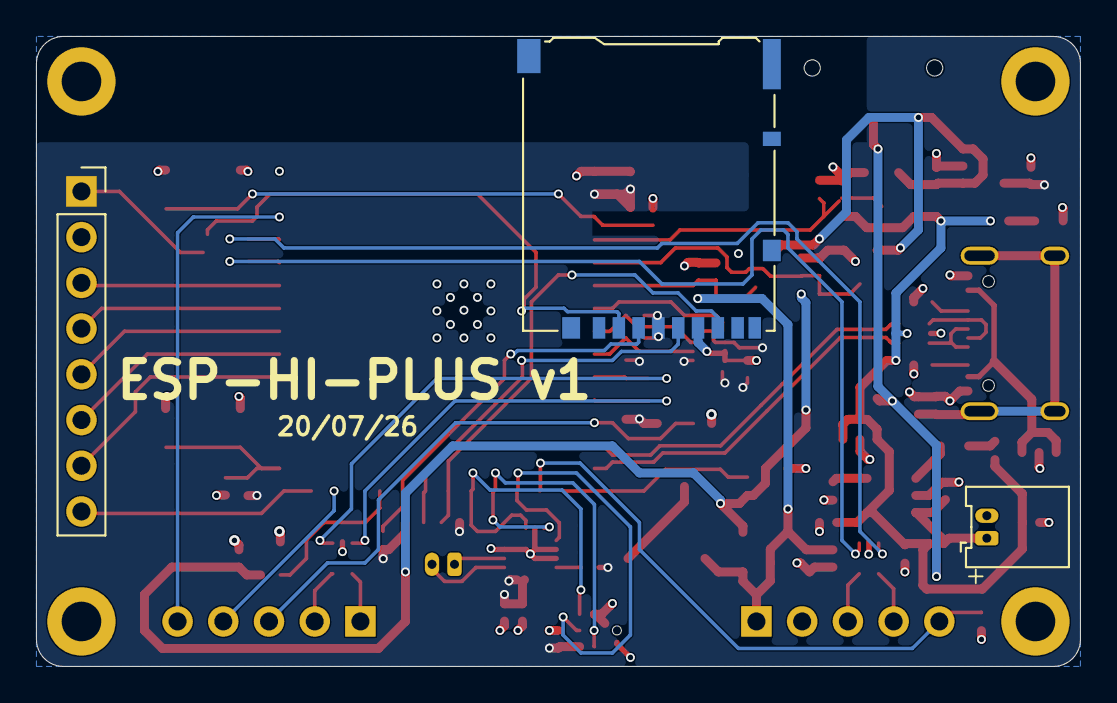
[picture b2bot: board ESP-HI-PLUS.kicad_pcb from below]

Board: 4 copper layers, 58.0 x 35.0 mm, 88 parts (3 on the bottom side), 62 nets.

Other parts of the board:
Ref**: Val**; OSHW_Logo_5mm

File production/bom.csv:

Designator,Footprint,Quantity,Value,LCSC Part #
BT1,Molex_PicoBlade_53048-0210_1x02_P1.25mm_Horizontal,1,Battery_Cell,
C1,0402,1,15p,
"C10, C14, C3, C4, C5, C6",0402,6,10u,
"C11, C13, C15, C16, C17, C18, C7, C8, C9",0402,9,0u1,
C12,0805,1,100u,
C19,0402,1,4n7,
C2,0402,1,1u,
"D1, D7, D8",SOT-666,3,USBLC6-2P6,
"D10, D11, D9",SOT-23,3,BAT54S,
D12,LED_WS2812B-2020_PLCC4_2.0x2.0mm,1,WS2812B-2020,
D2,0603,1,ORANGE,
D4,0603,1,RED,
D5,D_SOD-323F,1,PMEG4010CEJ,
D6,D_SOD-123F,1,SMF6.8CA,
F1,1812,1,MF-MSMF200,
J1,USB_C_Receptacle_HCTL_HC-TYPE-C-16P-01A,1,USB_C_Receptacle_USB2.0_14P,
J2,PinSocket_1x08_P2.54mm_Vertical,1,"2"" IPS LCD",
"J3, J4",PinHeader_1x05_P2.54mm_Vertical,2,PR5L4015-5P-C-F,
J5,microSD_HC_Hirose_DM3AT-SF-PEJM5,1,Micro_SD_Card,
LS1,Molex_PicoBlade_53048-0210_1x02_P1.25mm_Horizontal,1,Speaker,
MK1,InvenSense_ICS-43434-6_3.5x2.65mm,1,ICS-43434,
Q1,SOT-23,1,AO3401A,
Q2,SOT-723,1,NTK3139P,
"R1, R13, R2, R30, R31, R32, R33",0402,7,10k,
"R10, R11, R3, R4, R5, R6",0402,6,5k1,
"R12, R21, R23, R25, R7",0402,5,100k,
R14,0402,1,2k1,
R15,0402,1,634k,
"R17, R18, R19, R20",0402,4,100,
"R22, R24, R26",0402,3,33k,
R27,0402,1,1M,
"R28, R29",0402,2,47k,
"R8, R9",0402,2,3k3,
"SW1, SW2",SW_Push_1P1T_NO_Vertical_Wuerth_434133025816,2,SKRPACE010,
SW3,SW_SPDT_CK_JS102011SAQN,1,JS102011SAQN,
"U1, U6",SOT-23-5,2,MAX40200AUK,
U2,ESP32-S3-WROOM-1,1,ESP32-S3-WROOM-1,
U3,SOT-23-5,1,TLV75733PDBV,
U5,SOT-23-5_HandSoldering,1,TP4065,
U7,TQFN-16-1EP_3x3mm_P0.5mm_EP1.23x1.23mm,1,MAX98357A,
U8,LGA14_LSM6_STM,1,LSM6DSV16X,
